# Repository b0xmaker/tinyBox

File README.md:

# tinyBox
based off adafruit trinket m0, thanks to lady ada for great resources! 
https://www.adafruit.com/product/3500
designed for EE 101
BOM list: https://www.digikey.com/BOM/View?id=8443052

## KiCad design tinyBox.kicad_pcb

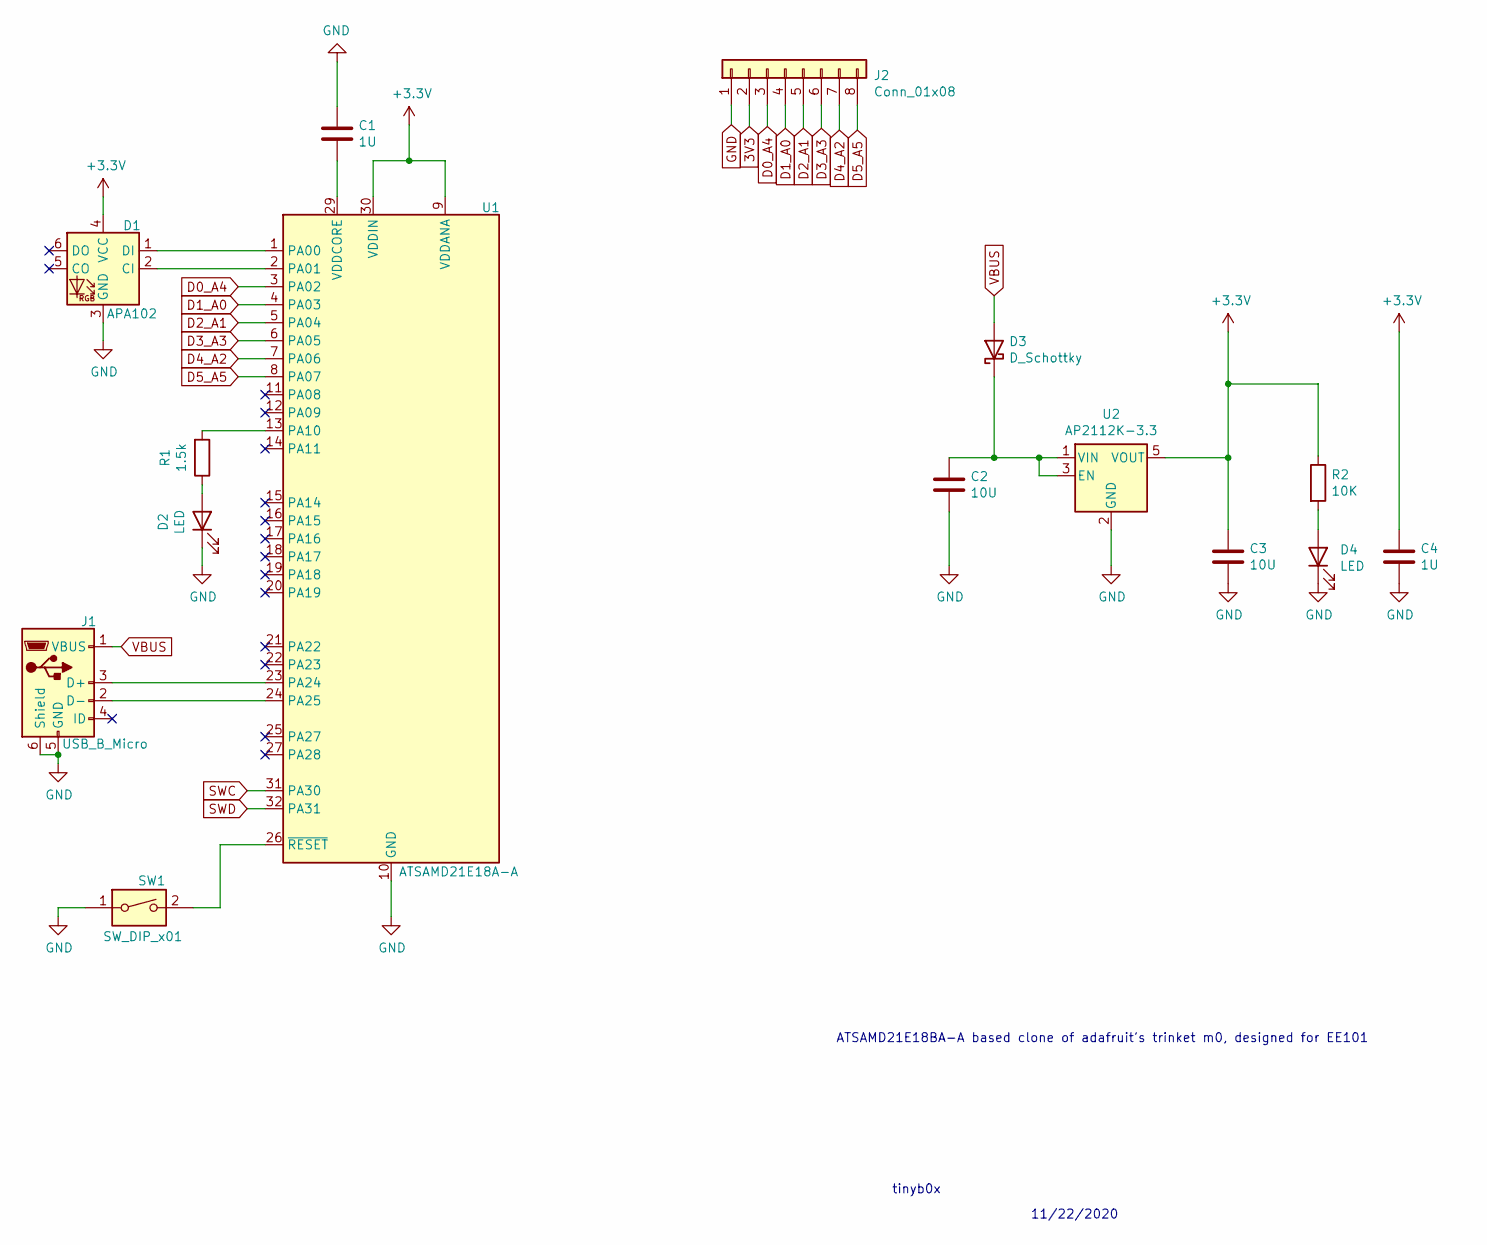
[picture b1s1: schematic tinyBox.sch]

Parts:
C1, C4: 1U; C_0805_2012Metric_Pad1.18x1.45mm_HandSolder
C2, C3: 10U; C_0805_2012Metric_Pad1.18x1.45mm_HandSolder
D1: APA102; LED_RGB_5050-6
D2, D4: LED; LED_0805_2012Metric_Pad1.15x1.40mm_HandSolder
D3: D_Schottky; D_0805_2012Metric_Pad1.15x1.40mm_HandSolder
J1: USB_B_Micro; USB_Micro-B_Molex_47346-0001
J2: Conn_01x08; PinHeader_1x08_P2.54mm_Vertical
R1: 1.5k; R_0805_2012Metric_Pad1.20x1.40mm_HandSolder
R2: 10K; R_0805_2012Metric_Pad1.20x1.40mm_HandSolder
SW1: SW_DIP_x01; SW_SPST_CK_RS282G05A3
U1: ATSAMD21E18A-A; TQFP-32_7x7mm_P0.8mm
U2: AP2112K-3.3; SOT-23-5

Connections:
D0_A4: J2.3, U1.3 (PA02)
D1_A0: J2.4, U1.4 (PA03)
D2_A1: J2.5, U1.5 (PA04)
D3_A3: J2.6, U1.6 (PA05)
D4_A2: J2.7, U1.7 (PA06)
D5_A5: J2.8, U1.8 (PA07)
GND: C1.1, C2.2, C3.2, C4.2, D1.3 (GND), D2.1 (K), D4.1 (K), J1.5 (GND), J1.6 (Shield), J2.1, SW1.1, U1.10 (GND), U1.28 (GND), U2.2 (GND)
unnamed: C1.2, U1.29 (VDDCORE)
unnamed: C2.1, D3.1 (K), U2.1 (VIN), U2.3 (EN)
unnamed: D1.1 (DI), U1.1 (PA00)
unnamed: D1.2 (CI), U1.2 (PA01)
unnamed: D2.2 (A), R1.1
unnamed: D4.2 (A), R2.2
unnamed: J1.2 (D-), U1.24 (PA25)
unnamed: J1.3 (D+), U1.23 (PA24)
unnamed: R1.2, U1.13 (PA10)
unnamed: SW1.2, U1.26 (~RESET)
SWC: U1.31 (PA30)
SWD: U1.32 (PA31)
VBUS: D3.2 (A), J1.1 (VBUS)

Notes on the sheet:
11/22/2020
ATSAMD21E18BA-A based clone of adafruit's trinket m0, designed for EE101
tinyb0x

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
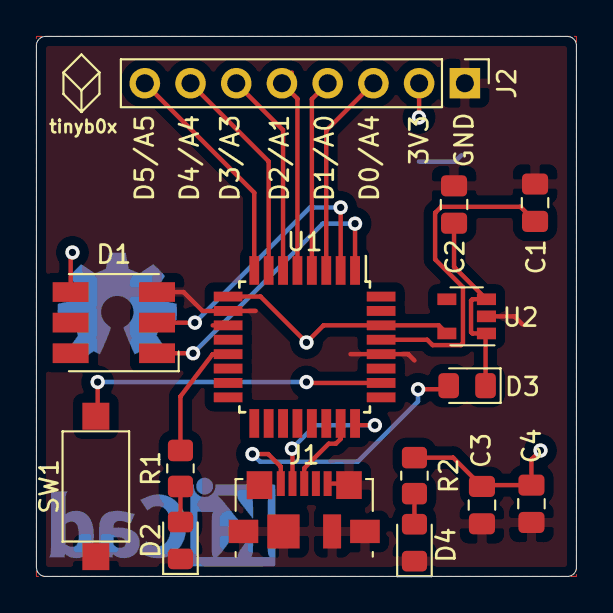
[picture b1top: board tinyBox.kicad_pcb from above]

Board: 2 copper layers, 30.0 x 30.0 mm, 15 parts (0 on the bottom side), 19 nets.
